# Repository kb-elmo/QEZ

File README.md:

# QEZ

[![CC BY-NC-SA 4.0][cc-by-nc-sa-shield]][cc-by-nc-sa]

### A seamless, gasketmounted QAZ-like 40% keyboard

---

[STEP files for the case](case/)

[KiCAD PCB files](pcb/)

[Gerbers for PCB production](pcb/gerbers/)

[JLCPCB BOM](pcb/fab/qez_bom_jlc.csv)

[JLCPCB CPL](pcb/fab/qez_cpl_jlc.csv)

[Vial-QMK firmware](firmware/)

---

This work is licensed under a
[Creative Commons Attribution-NonCommercial-ShareAlike 4.0 International License][cc-by-nc-sa].

[![CC BY-NC-SA 4.0][cc-by-nc-sa-image]][cc-by-nc-sa]

[cc-by-nc-sa]: http://creativecommons.org/licenses/by-nc-sa/4.0/
[cc-by-nc-sa-image]: https://licensebuttons.net/l/by-nc-sa/4.0/88x31.png
[cc-by-nc-sa-shield]: https://img.shields.io/badge/License-CC%20BY--NC--SA%204.0-lightgrey.svg

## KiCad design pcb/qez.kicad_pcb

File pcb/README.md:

# QEZ PCB

### Features

- Powered by an Atmega32u2
- Basic ESD and overvoltage protection
- Centered USB type-C port for a detachable cable
- Multiple layout options (see below)
- Fully programmable using [QMK](https://qmk.fm) and [Vial](https://get.vial.today)

---

### Supported layouts

---

### Preview

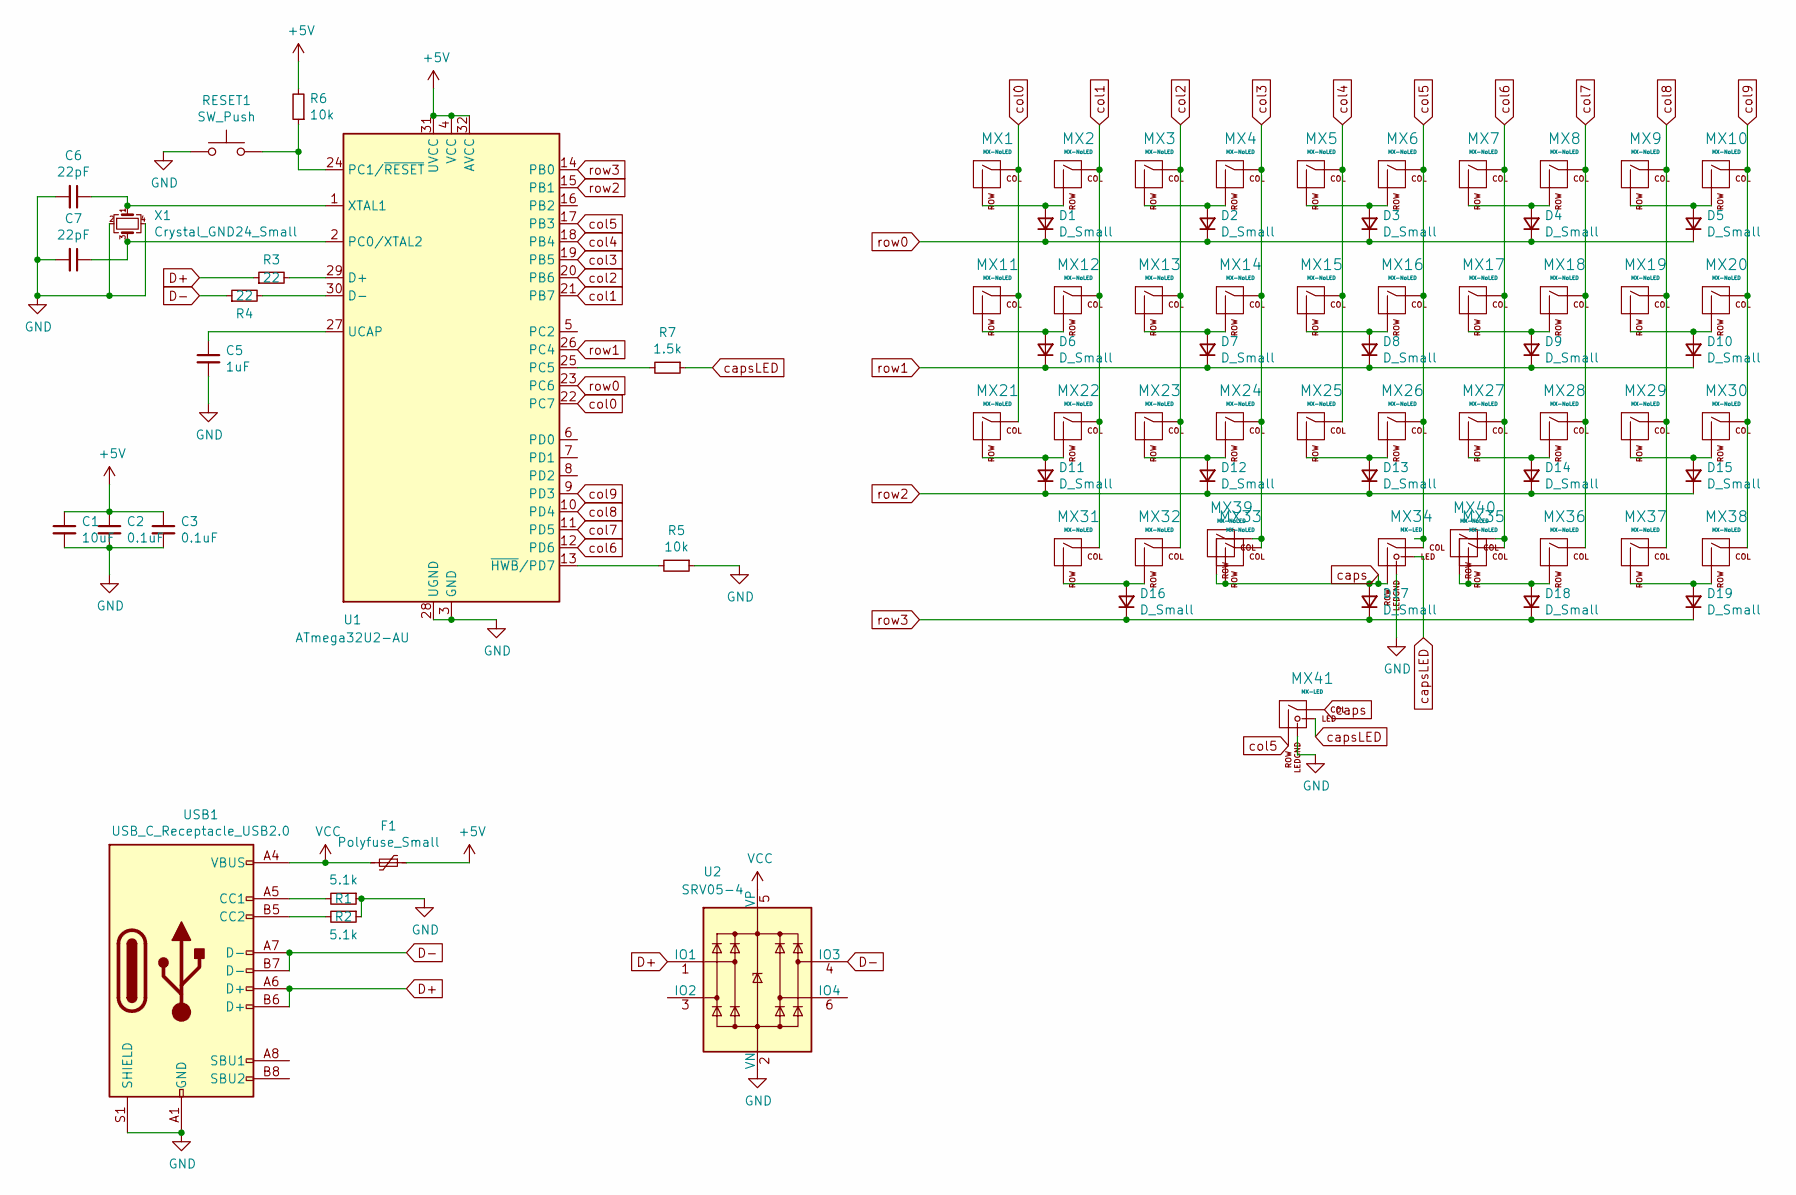
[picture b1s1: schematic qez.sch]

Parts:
C1: 10uF; C_0805_2012Metric; LCSC C91245
C2, C3: 0.1uF; C_0805_2012Metric; LCSC C49678
C5: 1uF; C_0805_2012Metric; LCSC C28323
C6, C7: 22pF; C_0805_2012Metric; LCSC C1804
D1, D2, D3, D4, D5, D6, D7, D8, D9, D10, D11, D12, D13, D14, D15, D16, D17, D18, D19: D_Small; D_SOT-23_ANK; LCSC C68978
F1: Polyfuse_Small; Fuse_1206_3216Metric; LCSC C69688
MX1, MX2, MX3, MX4, MX5, MX6, MX7, MX8, MX9, MX12, MX13, MX14, MX15, MX16, MX17, MX18, MX19, MX20, MX22, MX23, MX24, MX25, MX26, MX27, MX28, MX29, MX31, MX32, MX36, MX37, MX38: MX-NoLED; MXOnly-1U-NoLED
MX10, MX11: MX-NoLED; MXOnly-1.25U-NoLED
MX21: MX-NoLED; MXOnly-1.75U-NoLED
MX30: MX-NoLED; MXOnly-1.5U-NoLED
MX33: MX-NoLED; MXOnly-2.75U-ReversedStabilizers-NoLED
MX34: MX-LED; MXOnly-1.25U
MX35, MX39: MX-NoLED; MXOnly-2.25U-ReversedStabilizers-NoLED
MX40: MX-NoLED; MXOnly-2U-ReversedStabilizers-NoLED
MX41: MX-LED; MXOnly-6.25U-ReversedStabilizers-flippedLED
R1, R2: 5.1k; R_0805_2012Metric; LCSC C27834
R3, R4: 22; R_0805_2012Metric; LCSC C17561
R5, R6: 10k; R_0805_2012Metric; LCSC C17414
R7: 1.5k; R_0805_2012Metric; LCSC C4310
RESET1: SW_Push; SW_SPST_TL3342; LCSC C318884
U1: ATmega32U2-AU; TQFP-32_7x7mm_P0.8mm; LCSC C618733
U2: SRV05-4; SOT-23-6; LCSC C85364
USB1: USB_C_Receptacle_USB2.0; USB_C_Receptacle_HRO_TYPE-C-31-M-12; LCSC C165948
X1: Crystal_GND24_Small; Crystal_SMD_3225-4Pin_3.2x2.5mm; LCSC C13738

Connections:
+5V: C1.1, C2.1, C3.1, F1.1, R6.2, U1.4 (VCC), U1.31 (UVCC), U1.32 (AVCC)
D+: R3.1, U2.1 (IO1), USB1.A6 (D+), USB1.B6 (D+)
D-: R4.1, U2.4 (IO3), USB1.A7 (D-), USB1.B7 (D-)
GND: C1.2, C2.2, C3.2, C5.2, C6.2, C7.2, MX34.4 (LEDGND), MX41.4 (LEDGND), R1.1, R2.1, R5.1, RESET1.1, U1.3 (GND), U1.28 (UGND), U2.2 (VN), USB1.A1 (GND), USB1.A12 (GND), USB1.B1 (GND), USB1.B12 (GND), USB1.S1 (SHIELD), X1.2, X1.4; also elsewhere on the board
unnamed: C5.1, U1.27 (UCAP)
unnamed: C6.1, U1.1 (XTAL1), X1.1
unnamed: C7.1, U1.2 (PC0/XTAL2), X1.3
unnamed: D1.2 (A), MX1.2 (ROW), MX2.2 (ROW)
unnamed: D2.2 (A), MX3.2 (ROW), MX4.2 (ROW)
unnamed: D3.2 (A), MX5.2 (ROW), MX6.2 (ROW)
unnamed: D4.2 (A), MX7.2 (ROW), MX8.2 (ROW)
unnamed: D5.2 (A), MX9.2 (ROW), MX10.2 (ROW)
unnamed: D6.2 (A), MX11.2 (ROW), MX12.2 (ROW)
unnamed: D7.2 (A), MX13.2 (ROW), MX14.2 (ROW)
unnamed: D8.2 (A), MX15.2 (ROW), MX16.2 (ROW)
unnamed: D9.2 (A), MX17.2 (ROW), MX18.2 (ROW)
unnamed: D10.2 (A), MX19.2 (ROW), MX20.2 (ROW)
unnamed: D11.2 (A), MX21.2 (ROW), MX22.2 (ROW)
unnamed: D12.2 (A), MX23.2 (ROW), MX24.2 (ROW)
unnamed: D13.2 (A), MX25.2 (ROW), MX26.2 (ROW)
unnamed: D14.2 (A), MX27.2 (ROW), MX28.2 (ROW)
unnamed: D15.2 (A), MX29.2 (ROW), MX30.2 (ROW)
unnamed: D16.2 (A), MX31.2 (ROW), MX32.2 (ROW)
unnamed: D18.2 (A), MX35.2 (ROW), MX36.2 (ROW), MX40.2 (ROW)
unnamed: D19.2 (A), MX37.2 (ROW), MX38.2 (ROW)
unnamed: R1.2, USB1.A5 (CC1)
unnamed: R2.2, USB1.B5 (CC2)
unnamed: R3.2, U1.29 (D+)
unnamed: R4.2, U1.30 (D-)
unnamed: R5.2, U1.13 (~HWB~/PD7)
unnamed 30: R6.1, RESET1.2, U1.24 (PC1/~RESET); also elsewhere on the board
unnamed: R7.2, U1.25 (PC5)
VCC: F1.2, U2.5 (VP), USB1.A4 (VBUS), USB1.A9 (VBUS), USB1.B4 (VBUS), USB1.B9 (VBUS)
caps: D17.2 (A), MX33.2 (ROW), MX34.2 (ROW), MX39.2 (ROW), MX41.1 (COL)
capsLED: MX34.3 (LED), MX41.3 (LED), R7.1
col0: MX1.1 (COL), MX11.1 (COL), MX21.1 (COL), U1.22 (PC7)
col1: MX2.1 (COL), MX12.1 (COL), MX22.1 (COL), MX31.1 (COL), U1.21 (PB7)
col2: MX3.1 (COL), MX13.1 (COL), MX23.1 (COL), MX32.1 (COL), U1.20 (PB6)
col3: MX4.1 (COL), MX14.1 (COL), MX24.1 (COL), MX33.1 (COL), MX39.1 (COL), U1.19 (PB5)
col4: MX5.1 (COL), MX15.1 (COL), MX25.1 (COL), U1.18 (PB4)
col5: MX6.1 (COL), MX16.1 (COL), MX26.1 (COL), MX34.1 (COL), MX41.2 (ROW), U1.17 (PB3)
col6: MX7.1 (COL), MX17.1 (COL), MX27.1 (COL), MX35.1 (COL), MX40.1 (COL), U1.12 (PD6)
col7: MX8.1 (COL), MX18.1 (COL), MX28.1 (COL), MX36.1 (COL), U1.11 (PD5)
col8: MX9.1 (COL), MX19.1 (COL), MX29.1 (COL), MX37.1 (COL), U1.10 (PD4)
col9: MX10.1 (COL), MX20.1 (COL), MX30.1 (COL), MX38.1 (COL), U1.9 (PD3)
row0: D1.1 (K), D2.1 (K), D3.1 (K), D4.1 (K), D5.1 (K), U1.23 (PC6)
row1: D6.1 (K), D7.1 (K), D8.1 (K), D9.1 (K), D10.1 (K), U1.26 (PC4)
row2: D11.1 (K), D12.1 (K), D13.1 (K), D14.1 (K), D15.1 (K), U1.15 (PB1)
row3: D16.1 (K), D17.1 (K), D18.1 (K), D19.1 (K), U1.14 (PB0)

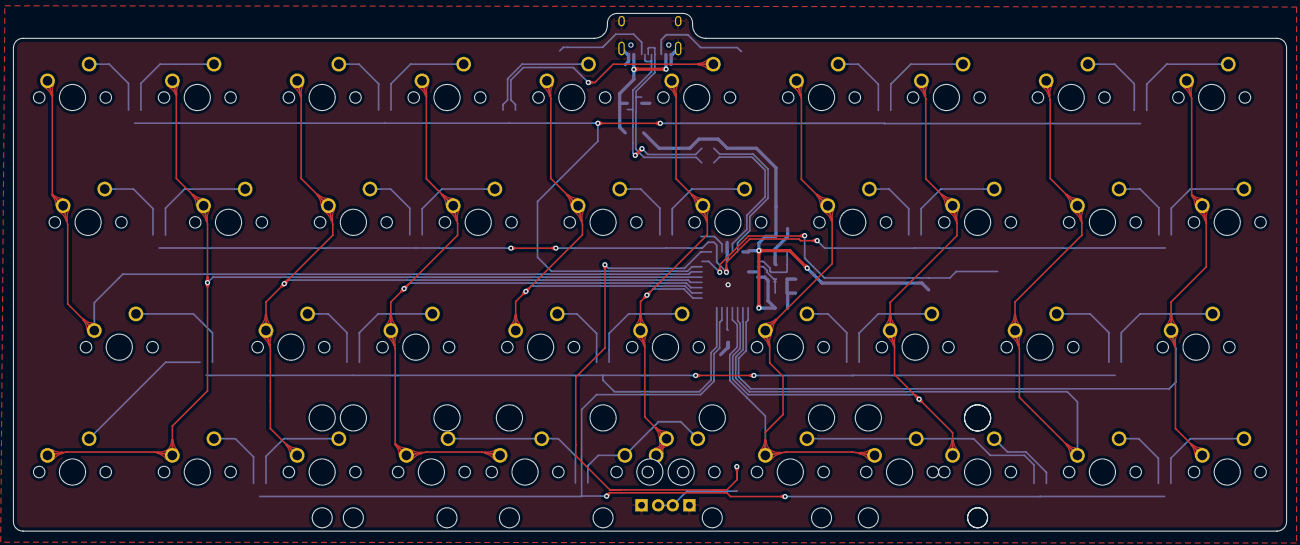
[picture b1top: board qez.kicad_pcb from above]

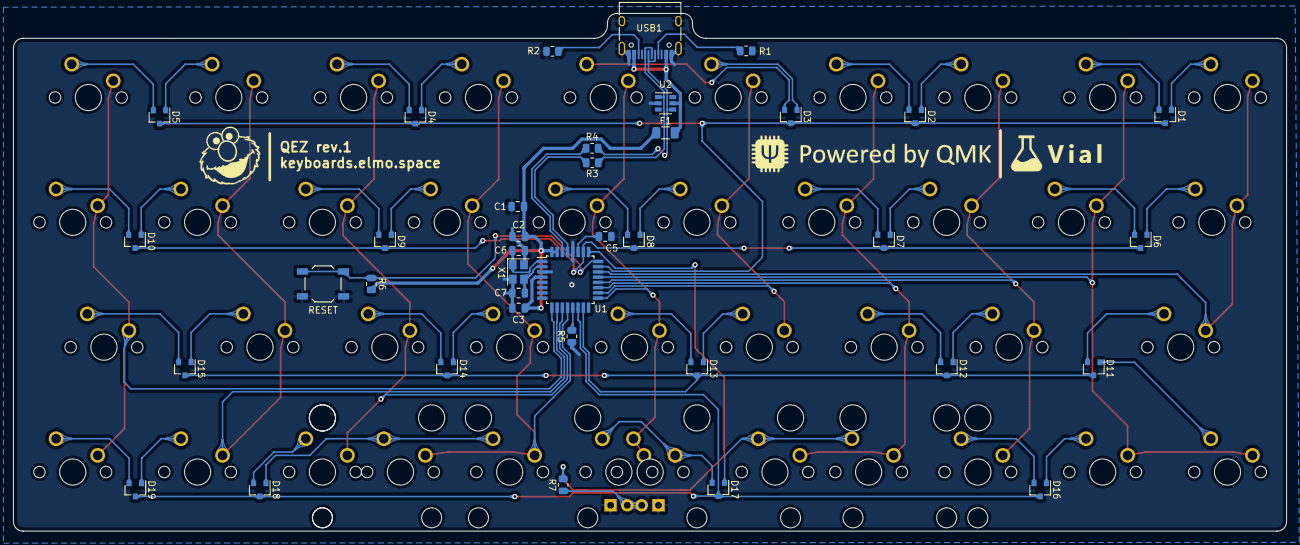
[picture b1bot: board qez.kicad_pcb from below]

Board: 2 copper layers, 194.3 x 79.0 mm, 79 parts (38 on the bottom side), 49 nets.

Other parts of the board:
RESET: SW_Push; SW_SPST_TL3342

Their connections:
GND: RESET.1; also elsewhere on the board
unnamed 30: RESET.2; also elsewhere on the board

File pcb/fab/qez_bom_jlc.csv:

"Comment","Designator","Footprint","LCSC Part #"
"10uF","C1","C_0805_2012Metric","C91245"
"0.1uF","C2,C3","C_0805_2012Metric","C49678"
"1uF","C5","C_0805_2012Metric","C28323"
"22pF","C6,C7","C_0805_2012Metric","C1804"
"D_Small","D1,D5,D4,D3,D2,D6,D10,D9,D8,D7,D11,D15,D14,D13,D12,D18,D17,D16,D19","D_SOT-23_ANK","C68978"
"Polyfuse_Small","F1","Fuse_1206_3216Metric","C69688"
"5.1k","R1,R2","R_0805_2012Metric","C27834"
"22","R3,R4","R_0805_2012Metric","C17561"
"10k","R5,R6","R_0805_2012Metric","C17414"
"1.5k","R7","R_0805_2012Metric","C4310"
"SW_Push","RESET","SW_SPST_TL3342","C318884"
"SRV05-4","U2","SOT-23-6","C85364"
"USB_C_Receptacle_USB2.0","USB1","USB_C_Receptacle_HRO_TYPE-C-31-M-12","C165948"
"Crystal_GND24_Small","X1","Crystal_SMD_3225-4Pin_3.2x2.5mm","C13738"

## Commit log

2021-08-18 change readme
2021-08-18 remove gerber zip
2021-08-23 update firmware
2021-08-23 add MCU part number for JLC
2021-08-27 fix step files
2021-11-02 add hhkb top
2021-11-02 add WKL top
2023-12-10 Added universal plate in 4mm (like other plates) and 5mm (real thickplate, no gap between PCB and plate)
